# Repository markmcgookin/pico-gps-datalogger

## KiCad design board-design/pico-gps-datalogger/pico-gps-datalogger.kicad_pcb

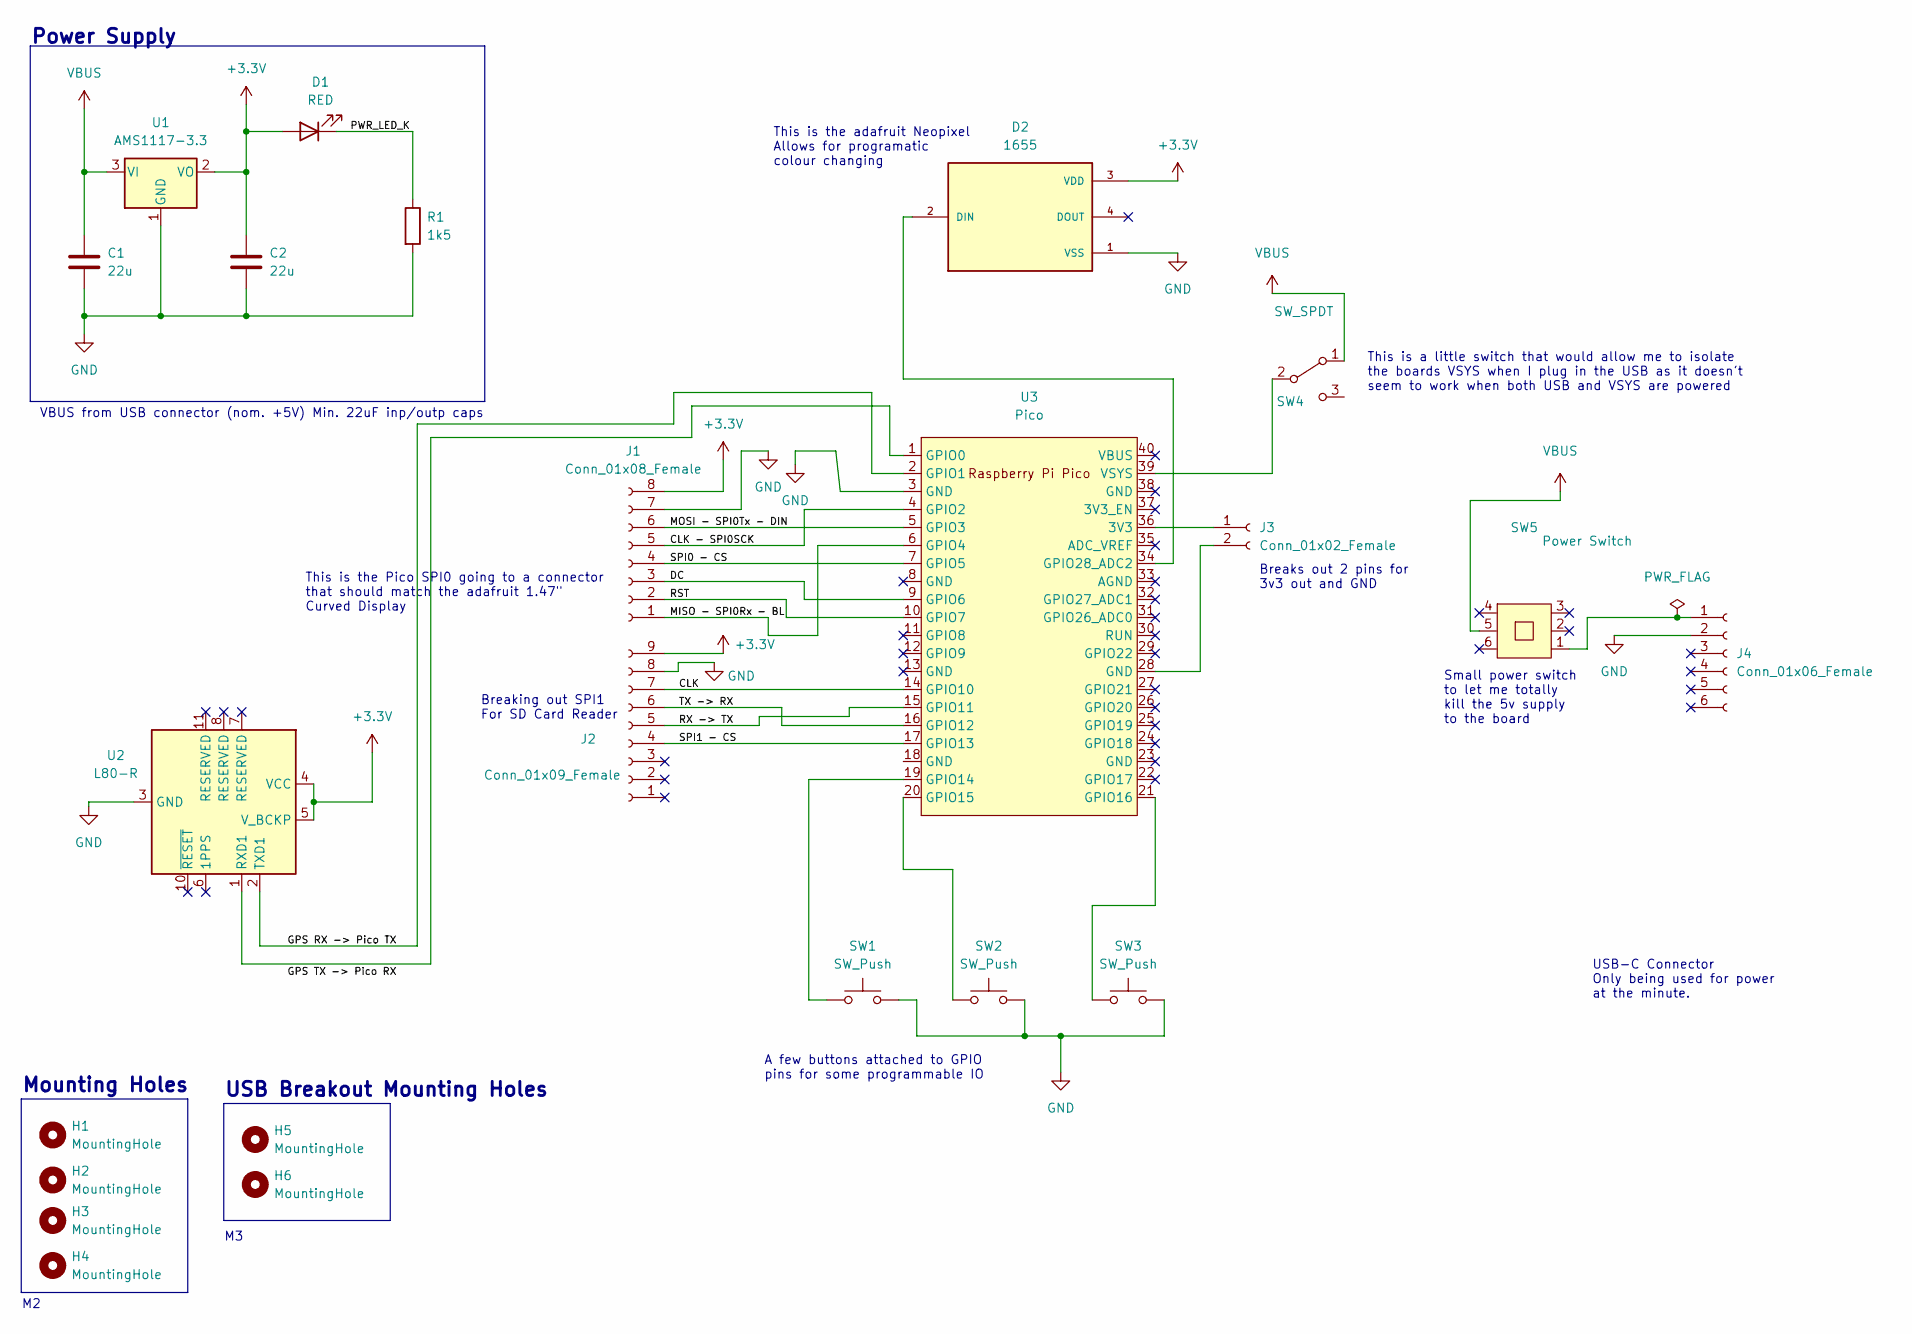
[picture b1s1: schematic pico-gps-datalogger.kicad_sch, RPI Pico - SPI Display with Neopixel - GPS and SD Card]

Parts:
C1, C2: 22u; C_0603_1608Metric
D1: RED; LED_0603_1608Metric
D2: 1655; LED_1655; PARTREV 01
H1, H2, H3, H4: MountingHole; MountingHole_2.2mm_M2
H5, H6: MountingHole; MountingHole_3.2mm_M3
J1: Conn_01x08_Female; JST_PH_B8B-PH-K_1x08_P2.00mm_Vertical
J2: Conn_01x09_Female; PinHeader_1x09_P2.54mm_Vertical
J3: Conn_01x02_Female; PinHeader_1x02_P2.54mm_Vertical
J4: Conn_01x06_Female; PinHeader_1x06_P2.54mm_Vertical
R1: 1k5; R_0603_1608Metric
SW1, SW2, SW3: SW_Push; SW_PUSH_6mm_H5mm
SW4: SW_SPDT; SW_SPDT_PCM12
SW5: Power Switch; SW_DPDT_XLX
U1: AMS1117-3.3; SOT-223-3_TabPin2
U2: L80-R; Quectel_L80-R
U3: Pico; RPi_Pico_SMD_TH

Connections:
+3.3V: C2.1, D1.2 (A), D2.3 (VDD), J1.8, J2.9, U1.2 (VO), U2.4 (VCC), U2.5 (V_BCKP)
/CLK: J2.7, U3.14 (GPIO10)
/CLK - SPI0SCK: J1.5, U3.4 (GPIO2)
/DC: J1.3, U3.9 (GPIO6)
/GPS RX -> Pico TX: U2.2 (TXD1), U3.2 (GPIO1)
/MISO - SPI0Rx - BL: J1.1, U3.6 (GPIO4)
/MOSI - SPI0Tx - DIN: J1.6, U3.5 (GPIO3)
/PWR_LED_K: D1.1 (K), R1.1
/RST: J1.2, U3.10 (GPIO7)
/RX -> TX: J2.5, U3.15 (GPIO11)
/SPI0 - CS: J1.4, U3.7 (GPIO5)
/SPI1 - CS: J2.4, U3.17 (GPIO13)
/TX -> RX: J2.6, U3.16 (GPIO12)
GND: C1.2, C2.2, D2.1 (VSS), J1.7, J2.8, J4.2, R1.2, SW1.2, SW2.2, SW3.2, U1.1 (GND), U2.3 (GND), U2.12 (GND), U3.3 (GND)
unnamed: D2.2 (DIN), U3.34 (GPIO28_ADC2)
unnamed: J3.1, U3.36 (3V3)
unnamed: J3.2, U3.28 (GND)
unnamed: J4.1, SW5.1
unnamed: SW1.1, U3.19 (GPIO14)
unnamed: SW2.1, U3.20 (GPIO15)
unnamed: SW3.1, U3.21 (GPIO16)
unnamed: SW4.2 (B), U3.39 (VSYS)
unnamed: U2.1 (RXD1), U3.1 (GPIO0)
VBUS: C1.1, SW4.1 (A), SW5.5, U1.3 (VI)

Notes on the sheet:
A few buttons attached to GPIO pins for some programmable IO
Power Supply
Breaks out 2 pins for 3v3 out and GND
Mounting Holes
Small power switch to let me totally kill the 5v supply to the board
USB Breakout Mounting Holes
USB-C Connector Only being used for power at the minute.
Breaking out SPI1 For SD Card Reader
This is the adafruit Neopixel Allows for programatic colour changing
VBUS from USB connector (nom. +5V) Min. 22uF inp/outp caps
This is a little switch that would allow me to isolate the boards VSYS when I plug in the USB as it doesn't seem to work when both USB and VSYS are powered
This is the Pico SPI0 going to a connector that should match the adafruit 1.47" Curved Display

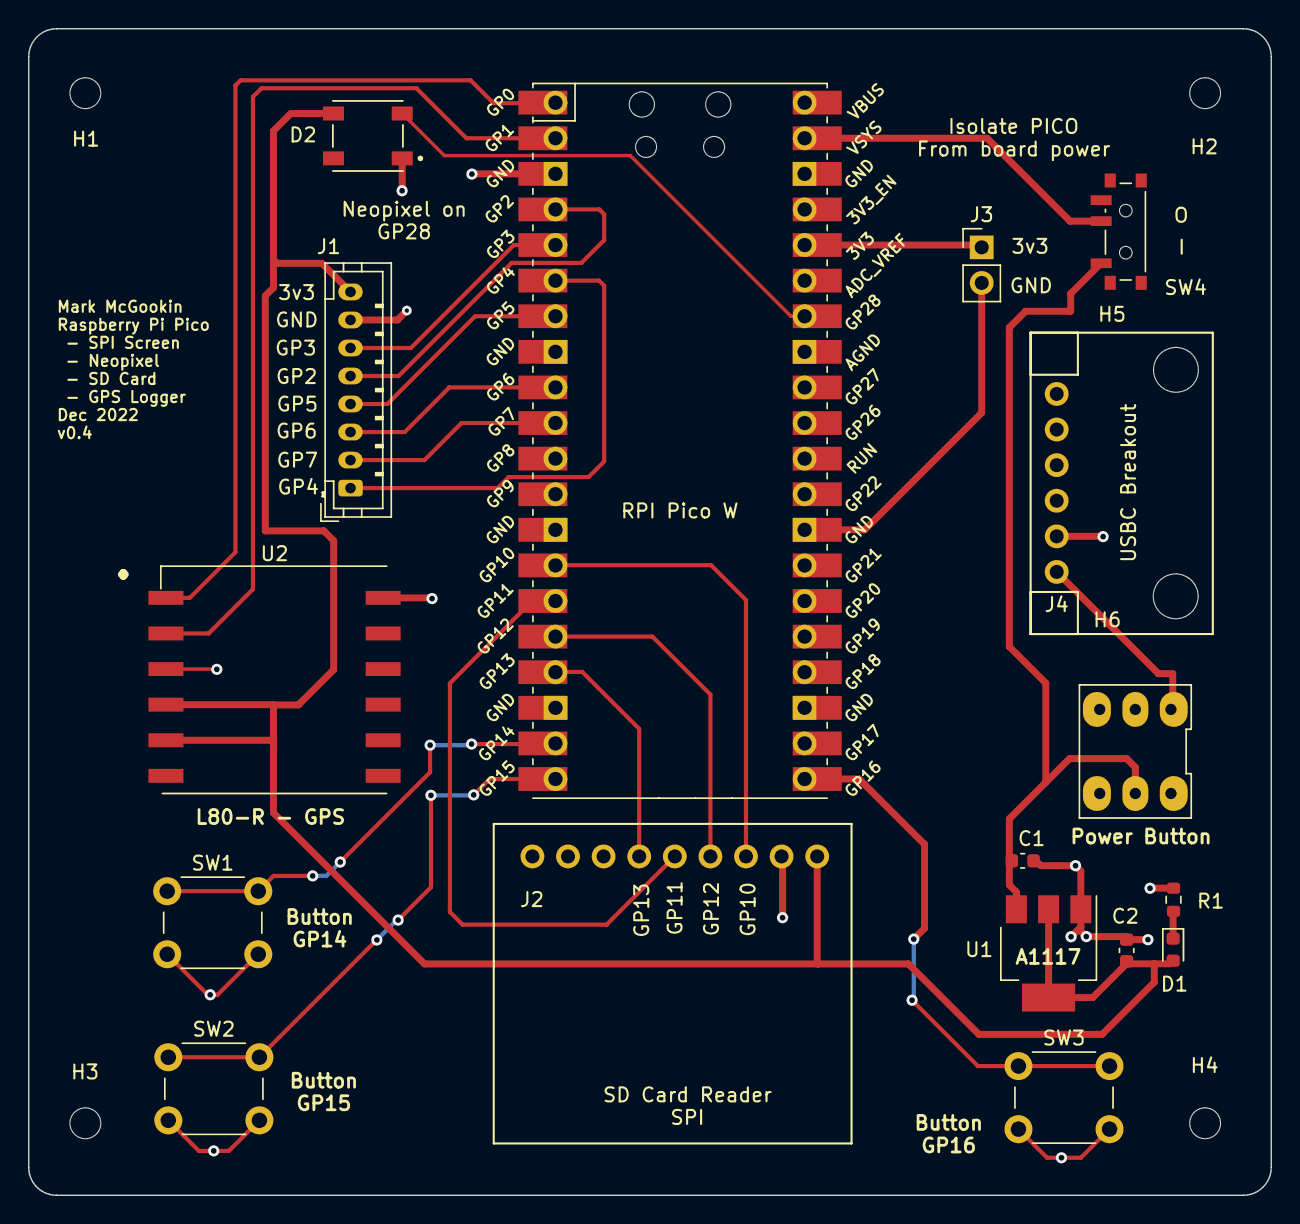
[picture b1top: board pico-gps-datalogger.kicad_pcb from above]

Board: 2 copper layers, 88.7 x 83.2 mm, 23 parts (0 on the bottom side), 24 nets.

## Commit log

2022-12-25 Got a working pico GPS reader (no logging yet) just prints
2022-12-25 Needs polished, and overwrites the file every time, but working logging GPS data to the SD card.
2022-12-26 tidied up the code, added some logic around the logfile name so a new one is created on each boot/run. Getting some more details
2022-12-27 updated to record a bit more info
2022-12-27 delted ds stores
2022-12-27 adding DS_Store to gitignore
2022-12-28 added board design, gerbers, step file etc
2022-12-28 Catching SD card not there, very messily outputting to screen. needs work
2022-12-28 updated pcb a bit, to power pico with 5v not 3v3 as it doesn't seem to like that. Added datasheet for GPS.
2023-01-01 updated design files again for rear copper on power switch
2023-01-11 added waveshare device version
2023-01-12 GPS working, screen working, SD Card working, Wifi working.
2023-01-12 added libs to repo
2023-01-15 Working before mode change switch development
2023-01-15 Got the mode switch working.... will reboot to change modes
2023-01-15 Added web server mode when switched to bottom.
2023-01-19 Added commented out code to show buttons
2023-01-19 Updated for buttons
2023-01-19 Added files for case design
